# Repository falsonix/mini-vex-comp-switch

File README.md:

# Mini VEXNet Comp Switch

<br>
This project was heavily inspired by https://github.com/Qlbbl1111/mini-comp-switch, and was originally just gonna be a fork of that, but I made my own version with the available resources.

I am not an employee of or associated with VEX Robotics, Inc. or Innovation First International, Inc. This project is only for personal usage and not for commercial sale.

# Bill of Materials
- 1x RJ45 Female Connector (https://www.lcsc.com/product-detail/C386758.html)
- 2x Slide Switch (https://www.lcsc.com/product-detail/C2939726.html)

# Sources
- https://content.vexrobotics.com/docs/VEXnet%20Comp%20Sw%20Diagram.pdf (Actual wiring, provided by VEX themselves)
- https://github.com/Qlbbl1111/mini-comp-switch (Original idea, tysm)

This work is licensed under <a href="https://creativecommons.org/licenses/by-nc-sa/4.0/">CC BY-NC-SA 4.0</a>

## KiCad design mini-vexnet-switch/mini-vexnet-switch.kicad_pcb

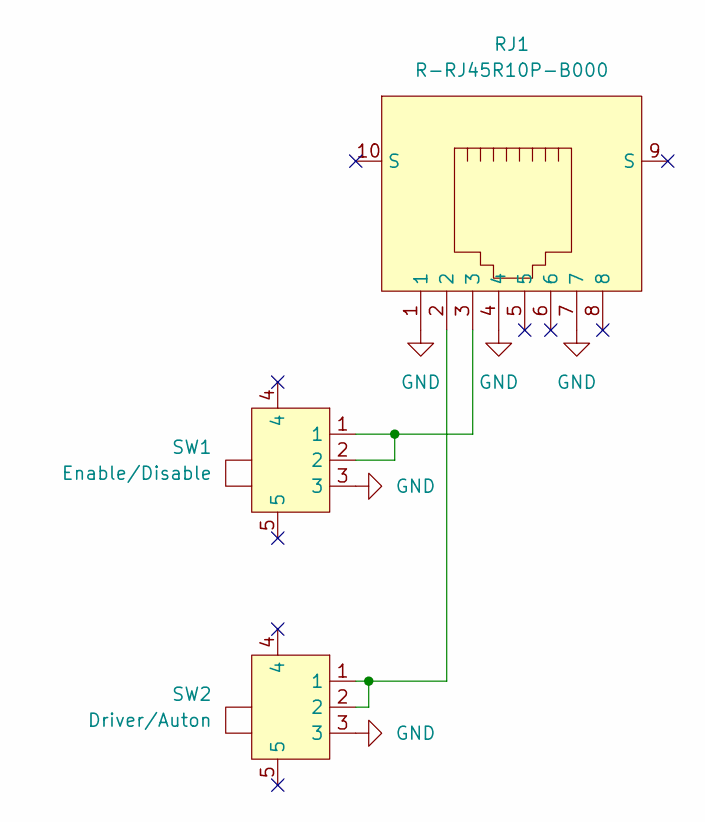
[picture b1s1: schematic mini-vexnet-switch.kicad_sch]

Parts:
RJ1: R-RJ45R10P-B000; RJ45-TH_R-RJ45R10P-B000; LCSC Part C386758
SW1: Enable/Disable; SW-TH_SS12D07VG4; LCSC Part C2939726
SW2: Driver/Auton; SW-TH_SS12D07VG4; LCSC Part C2939726

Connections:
GND: RJ1.1, RJ1.4, RJ1.7, SW1.3, SW2.3
unnamed: RJ1.2, SW2.1, SW2.2
unnamed: RJ1.3, SW1.1, SW1.2

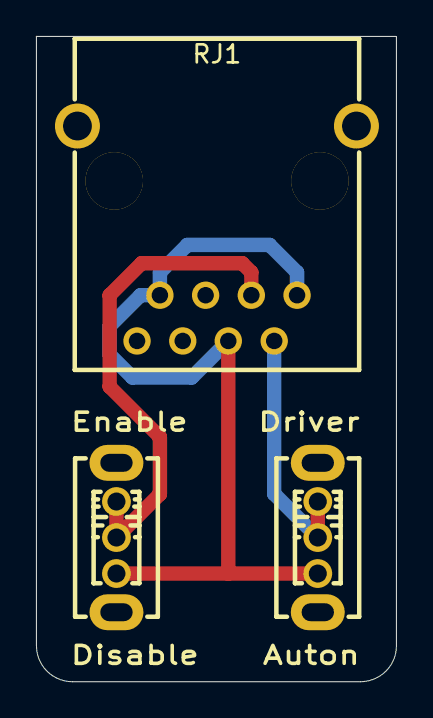
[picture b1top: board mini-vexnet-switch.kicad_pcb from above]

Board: 2 copper layers, 20.0 x 35.8 mm, 3 parts (0 on the bottom side), 3 nets.

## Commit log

2026-02-17 add license
2026-02-17 add gerber
2026-02-17 Rename mini-vexnet-switch.zip to gerber.zip
